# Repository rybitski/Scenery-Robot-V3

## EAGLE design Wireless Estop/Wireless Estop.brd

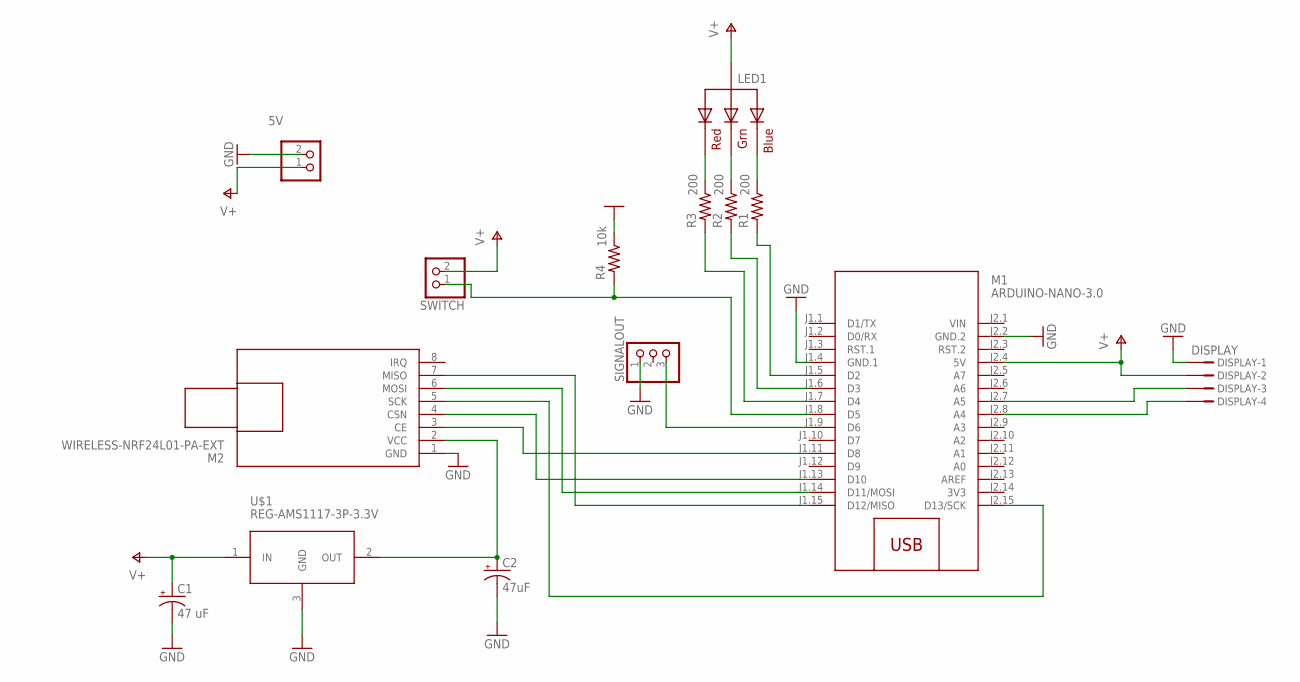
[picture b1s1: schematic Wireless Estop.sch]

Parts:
5V: JST_2PIN-THM; JST-PH-2-THM
C1: 47 uF; E2,5-5
C2: 47uF; E2,5-5
DISPLAY: DISPLAY; B4B-ZR
LED1: RGBLED_CA-5MM; LED5MMRGB
M1: ARDUINO-NANO-3.0
M2: WIRELESS-NRF24L01-PA-EXT
R1, R2, R3: 200; 0805-THM
R4: 10k; 0805-THM
SIGNALOUT: PINHD-1X3; 1X03
SWITCH: PINHD-1X2; 1X02
U$1: REG-AMS1117-3P-3.3V; REG-AMS1117-3P

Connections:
3V3: M1.J2.14 (3V3)
GND: 5V.2 (1), C1.-, C2.-, DISPLAY.1, M1.J1.4 (GND.1), M1.J2.2 (GND.2), M2.1 (GND), R4.1, SIGNALOUT.1, U$1.3 (GND)
unnamed: M1.J1.11 (D8), M2.3 (CE)
unnamed: M1.J1.13 (D10), M2.4 (CSN)
unnamed: M1.J2.15 (D13/SCK), M2.5 (SCK)
unnamed: M1.J1.14 (D11/MOSI), M2.6 (MOSI)
unnamed: M1.J1.15 (D12/MISO), M2.7 (MISO)
unnamed: C2.+, M2.2 (VCC), U$1.2 (OUT)
unnamed: LED1.4 (BLUE), R1.1
unnamed: LED1.3 (GREEN), R2.1
unnamed: LED1.1 (RED), R3.1
unnamed: M1.J1.5 (D2), R1.2
unnamed: M1.J1.6 (D3), R2.2
unnamed: M1.J1.7 (D4), R3.2
unnamed: DISPLAY.4, M1.J2.8 (A4)
unnamed: DISPLAY.3, M1.J2.7 (A5)
unnamed: M1.J1.8 (D5), R4.2, SWITCH.1
unnamed: M1.J1.9 (D6), SIGNALOUT.3
V+: 5V.1 (2), C1.+, DISPLAY.2, LED1.2 (VCC), M1.J2.4 (5V), SWITCH.2, U$1.1 (IN)
VIN: M1.J2.1 (VIN)

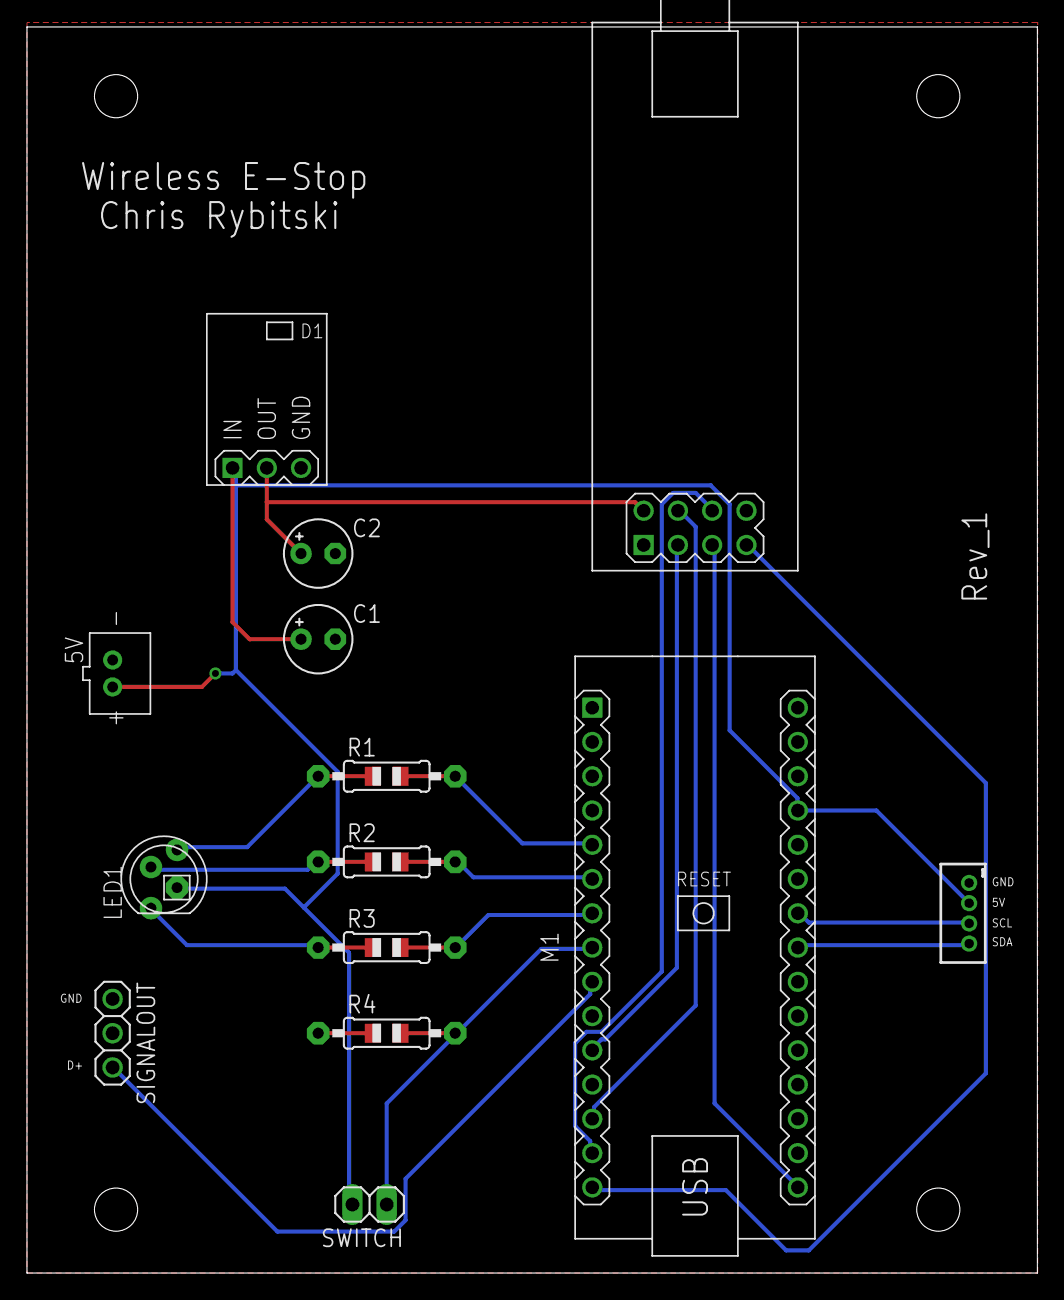
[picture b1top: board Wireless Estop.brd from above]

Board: 2 copper layers, 74.9 x 92.4 mm, 14 parts (0 on the bottom side), 18 nets.

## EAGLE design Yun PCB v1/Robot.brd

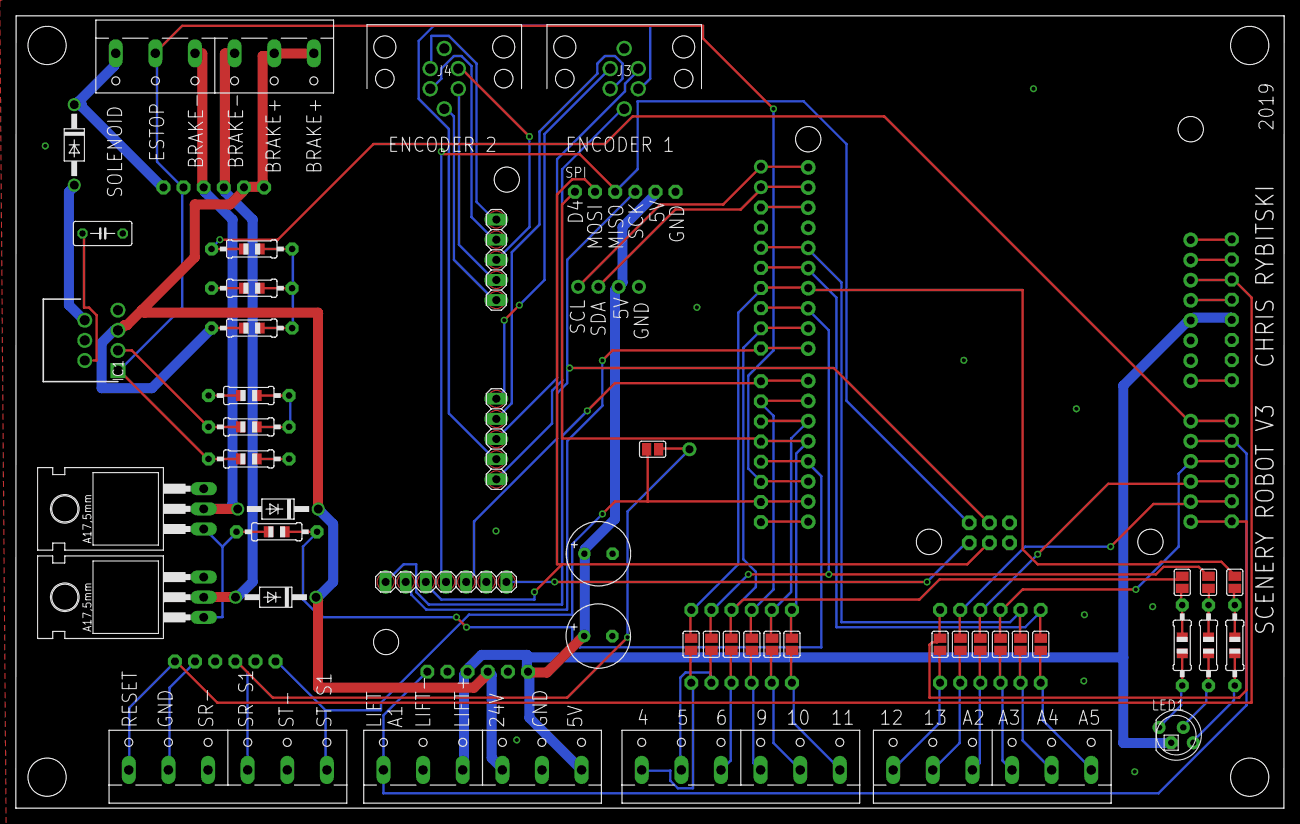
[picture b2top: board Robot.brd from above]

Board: 2 copper layers, 160.0 x 100.0 mm, 66 parts (1 on the bottom side), 73 nets.

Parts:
C5, C7: E3,5-8
C6: 0.1uF; C050-030X075
D1, D2, D3: 1N4004; DO41-10
IC1: DRV102T; TO127P470X1016X2195-7P
J3, J4: 4-2172081-2; 421720812
JP1, JP2: 1X05
JP3: 1X07
JP4, JP7, JP11, JP13, JP14, JP15, JP16, JP17: 1X06-CLEANBIG
JP5, JP6, JP8: 1X08-CLEANBIG
JP9, JP10, JP12, JP18, JP19, JP20, JP21: 1X01-CLEANBIG
LED1: RGBLED_CA-5MM; LED5MMRGB
PCB1: ARDUINO_UNO
Q3, Q4: TIP120; TO220AH
R5, R6, R7: 0805-THM
R9, R10, R14, R15: 10K; 0805-THM
R11: 2.2K; 0805-THM
R12: 20K; 0805-THM
R13: 51K; 0805-THM
SJ1, SJ2, SJ4, SJ5, SJ6, SJ7, SJ8, SJ9, SJ10, SJ11, SJ12, SJ13, SJ14, SJ15, SJ16, SJ17: SJ
SPI: 1X06-CLEANBIG
X1, X2, X3, X4, X5: W237-6

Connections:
3.3V: JP6.5, PCB1.3.3V
+5V: C5.+, C7.+, JP6.4, JP7.1, JP7.4, JP20.1, LED1.2, PCB1.5V, SPI.5, X3.3, X3.6
+24V: D2.C, D3.C, IC1.5, JP4.5, JP4.6, JP7.3, R10.2, X1.1, X1.2, X3.4
A0: JP11.6, PCB1.A0, R9.1, R9.2, R10.1, R11.2
A1: JP7.6, JP11.5, PCB1.A1, X3.1
A2: JP11.4, JP17.4, PCB1.A2, SJ14.1
A3: JP11.3, JP17.3, PCB1.A3, SJ15.1
A4: JP11.2, JP17.2, PCB1.A4, SJ16.1
A5: JP11.1, JP17.1, PCB1.A5, SJ17.1
AREF: JP8.1, PCB1.AREF
ATN: JP6.8, PCB1.N/C
BRAKE1: D3.A, JP4.3, Q3.C, X1.4
BRAKE2: D2.A, JP4.4, Q4.C, X1.3
D0: JP5.8, PCB1.0
D1: JP5.7, JP13.1, PCB1.1, SJ1.1, X2.6
D3: JP5.5, PCB1.3, R15.2
D4: JP5.4, JP16.6, PCB1.4, SJ2.1, SPI.1
D5: JP5.3, JP16.5, PCB1.5, SJ7.1
D6: JP5.2, JP16.4, PCB1.6, SJ8.1
D7: JP3.1, JP5.1, PCB1.7
D8: JP3.2, JP8.8, PCB1.8
D9: JP8.7, JP16.3, PCB1.9, SJ6.1, SJ9.1
D10: JP8.6, JP16.2, PCB1.10, SJ5.1, SJ10.1
D11: JP8.5, JP16.1, PCB1.11, SJ4.1, SJ11.1
D12: JP8.4, JP17.6, PCB1.12, SJ12.1
D13: JP8.3, JP17.5, PCB1.13, SJ13.1
ESTOP-IN: IC1.1, JP4.2, JP5.6, PCB1.2, R14.1, X1.5
GND: C5.-, C6.2, C7.-, IC1.4, JP3.6, JP6.2, JP6.3, JP7.2, JP7.5, JP8.2, JP13.2, JP13.4, JP21.1, PCB1.GND, PCB1.GND., PCB1.GND.., PCB1.GND_, Q3.E, Q4.E, R11.1, R13.2, R14.2, SPI.6, X2.3, X2.5, X3.2, X3.5
I/OREF: JP6.7, PCB1.I/OREF
MISO: JP3.4, PCB1.MISO, SPI.3
MOSI: JP3.3, PCB1.MOSI, SPI.2
unnamed: LED1.1, R7.2
unnamed: LED1.3, R6.2
unnamed: LED1.4, R5.2
unnamed: J3.1, JP1.2
unnamed: J3.2, JP1.3
unnamed: J3.5, JP1.4
unnamed: J3.4, JP1.5
unnamed: J4.1, JP2.2
unnamed: J4.2, JP2.3
unnamed: J4.4, JP2.5
unnamed: J4.5, JP2.4
unnamed: C6.1, IC1.2
unnamed: R12.2, R13.1
unnamed: IC1.3, R12.1
unnamed: D1.A, IC1.6
unnamed: Q3.B, Q4.B, R15.1
unnamed: JP14.1, SJ2.2, X4.6
unnamed: JP14.2, SJ7.2, X4.5
unnamed: JP14.3, SJ8.2, X4.4
unnamed: J3.6, JP1.1
unnamed: JP12.1, JP13.3, SJ1.2, X2.4
unnamed: J4.6, JP2.1
unnamed: JP14.4, SJ9.2, X4.3
unnamed: JP14.5, SJ10.2, X4.2
unnamed: JP14.6, SJ11.2, X4.1
unnamed: JP15.1, SJ12.2, X5.6
unnamed: JP15.2, SJ13.2, X5.5
unnamed: JP15.3, SJ14.2, X5.4
unnamed: JP15.4, SJ15.2, X5.3
unnamed: JP15.5, SJ16.2, X5.2
unnamed: JP15.6, SJ17.2, X5.1
unnamed: JP13.5, X2.2
unnamed: R7.1, SJ6.2
unnamed: R6.1, SJ5.2
unnamed: R5.1, SJ4.2
RESET: JP6.6, JP13.6, PCB1.RESET, X2.1
SCK: JP3.5, PCB1.SCK, SPI.4
SCL: JP10.1, JP18.1, PCB1.SCL
SDA: JP9.1, JP19.1, PCB1.SDA
SOLENOID: D1.C, JP4.1, X1.6
SPIV+: JP3.7, PCB1.+5V
VIN: JP6.1, PCB1.VIN

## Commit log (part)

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2019-03-13 Rename Wireless_Estop_v3_Remote.ino to Wireless Safety Stop/Arduino/Wireless_Estop_v3_Remote.ino
2019-03-13 Rename Wireless_Estop_v3_Robot.ino to Wireless Safety Stop/Arduino/Wireless_Estop_v3_Robot.ino
2019-03-14 Organized Folders
2019-03-15 Added Joes Stuff
    yay
2019-04-26 created wiki.md file (also in the wiki section)
2019-09-19 Merged
    Merging from joes repo
2019-09-19 Newer Update
2019-09-20 9/20 update
2019-09-20 Initial Commit
    Added firmware and middleware
2019-09-20 Adding firmware and middleware
    These files were previously missing and are required for operation.
2019-09-20 Friday meeting update
    Fixed drive code over specified distance
2019-09-25 Adding missing flash and pip
    Images required to complete YUN Guide and the pip tar file
2019-10-11 Created a method to parseJson and a test file
2019-10-11 safety stop code
2019-10-17 MiniBot
    Code for MiniBot subproject
2019-10-18 Kang speculative code
2019-10-30 Update accel/decel
    WIP
2019-11-01 Fixed drifting issue
    Dec still broken
2019-11-01 meeting
2019-11-06 MiniBot V1 Completion
2019-11-06 Rewrite for V2
2019-11-07 Stack Exchange implemented
2019-11-07 Changed from "and' to &&
2019-11-20 Added cue data to V3
2019-11-20 fixed bugs in last commit
2019-12-10 V3 folder
2019-12-28 Bump handlebars from 4.1.0 to 4.5.3 in /client-master
    Bumps [handlebars](https://github.com/wycats/handlebars.js) from 4.1.0 to 4.5.3.
    - [Release notes](https://github.com/wycats/handlebars.js/releases)
    - [Changelog](https://github.com/wycats/handlebars.js/blob/master/release-notes.md)
    - [Commits](https://github.com/wycats/handlebars.js/compare/v4.1.0...v4.5.3)
2020-03-14 Bump acorn from 5.7.3 to 5.7.4 in /client-master
    Bumps [acorn](https://github.com/acornjs/acorn) from 5.7.3 to 5.7.4.
    - [Release notes](https://github.com/acornjs/acorn/releases)
    - [Commits](https://github.com/acornjs/acorn/compare/5.7.3...5.7.4)
2020-06-06 Bump websocket-extensions from 0.1.3 to 0.1.4 in /client-master
    Bumps [websocket-extensions](https://github.com/faye/websocket-extensions-node) from 0.1.3 to 0.1.4.
    - [Release notes](https://github.com/faye/websocket-extensions-node/releases)
    - [Changelog](https://github.com/faye/websocket-extensions-node/blob/master/CHANGELOG.md)
    - [Commits](https://github.com/faye/websocket-extensions-node/compare/0.1.3...0.1.4)
2020-07-30 Bump elliptic from 6.4.1 to 6.5.3 in /client-master
    Bumps [elliptic](https://github.com/indutny/elliptic) from 6.4.1 to 6.5.3.
    - [Release notes](https://github.com/indutny/elliptic/releases)
    - [Commits](https://github.com/indutny/elliptic/compare/v6.4.1...v6.5.3)
2020-09-04 Bump handlebars from 4.1.0 to 4.7.6 in /client-master
    Bumps [handlebars](https://github.com/wycats/handlebars.js) from 4.1.0 to 4.7.6.
    - [Release notes](https://github.com/wycats/handlebars.js/releases)
    - [Changelog](https://github.com/handlebars-lang/handlebars.js/blob/master/release-notes.md)
    - [Commits](https://github.com/wycats/handlebars.js/compare/v4.1.0...v4.7.6)
2020-09-07 Bump http-proxy from 1.17.0 to 1.18.1 in /client-master
    Bumps [http-proxy](https://github.com/http-party/node-http-proxy) from 1.17.0 to 1.18.1.
    - [Release notes](https://github.com/http-party/node-http-proxy/releases)
    - [Changelog](https://github.com/http-party/node-http-proxy/blob/master/CHANGELOG.md)
    - [Commits](https://github.com/http-party/node-http-proxy/compare/1.17.0...1.18.1)
2021-03-09 Bump elliptic from 6.4.1 to 6.5.4 in /client-master
    Bumps [elliptic](https://github.com/indutny/elliptic) from 6.4.1 to 6.5.4.
    - [Release notes](https://github.com/indutny/elliptic/releases)
    - [Commits](https://github.com/indutny/elliptic/compare/v6.4.1...v6.5.4)
2021-03-30 Bump y18n from 3.2.1 to 3.2.2 in /client-master
    Bumps [y18n](https://github.com/yargs/y18n) from 3.2.1 to 3.2.2.
    - [Release notes](https://github.com/yargs/y18n/releases)
    - [Changelog](https://github.com/yargs/y18n/blob/master/CHANGELOG.md)
    - [Commits](https://github.com/yargs/y18n/commits)
2021-04-19 Bump ssri from 6.0.1 to 6.0.2 in /client-master
    Bumps [ssri](https://github.com/npm/ssri) from 6.0.1 to 6.0.2.
    - [Release notes](https://github.com/npm/ssri/releases)
    - [Changelog](https://github.com/npm/ssri/blob/v6.0.2/CHANGELOG.md)
    - [Commits](https://github.com/npm/ssri/compare/v6.0.1...v6.0.2)
2021-05-07 Bump url-parse from 1.4.4 to 1.5.1 in /client-master
    Bumps [url-parse](https://github.com/unshiftio/url-parse) from 1.4.4 to 1.5.1.
    - [Release notes](https://github.com/unshiftio/url-parse/releases)
    - [Commits](https://github.com/unshiftio/url-parse/compare/1.4.4...1.5.1)
2021-05-10 Bump hosted-git-info from 2.7.1 to 2.8.9 in /client-master
    Bumps [hosted-git-info](https://github.com/npm/hosted-git-info) from 2.7.1 to 2.8.9.
    - [Release notes](https://github.com/npm/hosted-git-info/releases)
    - [Changelog](https://github.com/npm/hosted-git-info/blob/v2.8.9/CHANGELOG.md)
    - [Commits](https://github.com/npm/hosted-git-info/compare/v2.7.1...v2.8.9)
2021-05-27 Bump dns-packet from 1.3.1 to 1.3.4 in /client-master
    Bumps [dns-packet](https://github.com/mafintosh/dns-packet) from 1.3.1 to 1.3.4.
    - [Release notes](https://github.com/mafintosh/dns-packet/releases)
    - [Changelog](https://github.com/mafintosh/dns-packet/blob/master/CHANGELOG.md)
    - [Commits](https://github.com/mafintosh/dns-packet/compare/v1.3.1...v1.3.4)
2021-06-07 Bump merge-deep from 3.0.2 to 3.0.3 in /client-master
    Bumps [merge-deep](https://github.com/jonschlinkert/merge-deep) from 3.0.2 to 3.0.3.
    - [Release notes](https://github.com/jonschlinkert/merge-deep/releases)
    - [Commits](https://github.com/jonschlinkert/merge-deep/compare/3.0.2...3.0.3)
    ---
    updated-dependencies:
    - dependency-name: merge-deep
2021-08-10 Bump path-parse from 1.0.6 to 1.0.7 in /client-master
    Bumps [path-parse](https://github.com/jbgutierrez/path-parse) from 1.0.6 to 1.0.7.
    - [Release notes](https://github.com/jbgutierrez/path-parse/releases)
    - [Commits](https://github.com/jbgutierrez/path-parse/commits/v1.0.7)
    ---
    updated-dependencies:
    - dependency-name: path-parse
2021-09-21 Bump tmpl from 1.0.4 to 1.0.5 in /client-master
    Bumps [tmpl](https://github.com/daaku/nodejs-tmpl) from 1.0.4 to 1.0.5.
    - [Release notes](https://github.com/daaku/nodejs-tmpl/releases)
    - [Commits](https://github.com/daaku/nodejs-tmpl/commits/v1.0.5)
    ---
    updated-dependencies:
    - dependency-name: tmpl
2021-10-05 Bump url-parse from 1.4.4 to 1.5.3 in /client-master
    Bumps [url-parse](https://github.com/unshiftio/url-parse) from 1.4.4 to 1.5.3.
    - [Release notes](https://github.com/unshiftio/url-parse/releases)
    - [Commits](https://github.com/unshiftio/url-parse/compare/1.4.4...1.5.3)
    ---
    updated-dependencies:
    - dependency-name: url-parse
2022-01-13 Bump follow-redirects from 1.6.1 to 1.14.7 in /client-master
    Bumps [follow-redirects](https://github.com/follow-redirects/follow-redirects) from 1.6.1 to 1.14.7.
    - [Release notes](https://github.com/follow-redirects/follow-redirects/releases)
    - [Commits](https://github.com/follow-redirects/follow-redirects/compare/v1.6.1...v1.14.7)
    ---
    updated-dependencies:
    - dependency-name: follow-redirects
2022-02-11 Bump ajv from 6.9.1 to 6.12.6 in /client-master
    Bumps [ajv](https://github.com/ajv-validator/ajv) from 6.9.1 to 6.12.6.
    - [Release notes](https://github.com/ajv-validator/ajv/releases)
    - [Commits](https://github.com/ajv-validator/ajv/compare/v6.9.1...v6.12.6)
    ---
    updated-dependencies:
    - dependency-name: ajv
2022-02-12 Bump follow-redirects from 1.6.1 to 1.14.8 in /client-master
    Bumps [follow-redirects](https://github.com/follow-redirects/follow-redirects) from 1.6.1 to 1.14.8.
    - [Release notes](https://github.com/follow-redirects/follow-redirects/releases)
    - [Commits](https://github.com/follow-redirects/follow-redirects/compare/v1.6.1...v1.14.8)
    ---
    updated-dependencies:
    - dependency-name: follow-redirects
2022-02-17 Bump url-parse from 1.4.4 to 1.5.7 in /client-master
    Bumps [url-parse](https://github.com/unshiftio/url-parse) from 1.4.4 to 1.5.7.
    - [Release notes](https://github.com/unshiftio/url-parse/releases)
    - [Commits](https://github.com/unshiftio/url-parse/compare/1.4.4...1.5.7)
    ---
    updated-dependencies:
    - dependency-name: url-parse
2022-06-01 Bump eventsource from 1.0.7 to 1.1.1 in /client-master
    Bumps [eventsource](https://github.com/EventSource/eventsource) from 1.0.7 to 1.1.1.
    - [Release notes](https://github.com/EventSource/eventsource/releases)
    - [Changelog](https://github.com/EventSource/eventsource/blob/master/HISTORY.md)
    - [Commits](https://github.com/EventSource/eventsource/compare/v1.0.7...v1.1.1)
    ---
    updated-dependencies:
2022-10-05 Bump css-what from 2.1.2 to 2.1.3 in /client-master
    Bumps [css-what](https://github.com/fb55/css-what) from 2.1.2 to 2.1.3.
    - [Release notes](https://github.com/fb55/css-what/releases)
    - [Commits](https://github.com/fb55/css-what/compare/v2.1.2...v2.1.3)
    ---
    updated-dependencies:
    - dependency-name: css-what
2022-11-18 Bump loader-utils and react-scripts in /client-master
    Bumps [loader-utils](https://github.com/webpack/loader-utils) to 2.0.4 and updates ancestor dependency [react-scripts](https://github.com/facebook/create-react-app/tree/HEAD/packages/react-scripts). 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
    Updates `loader-utils` from 1.2.3 to 2.0.4
    - [Release notes](https://github.com/webpack/loader-utils/releases)
    - [Changelog](https://github.com/webpack/loader-utils/blob/v2.0.4/CHANGELOG.md)
    - [Commits](https://github.com/webpack/loader-utils/compare/v1.2.3...v2.0.4)
    Updates `react-scripts` from 2.1.5 to 5.0.1
2022-12-03 Bump decode-uri-component from 0.2.0 to 0.2.2 in /client-master
    Bumps [decode-uri-component](https://github.com/SamVerschueren/decode-uri-component) from 0.2.0 to 0.2.2.
    - [Release notes](https://github.com/SamVerschueren/decode-uri-component/releases)
    - [Commits](https://github.com/SamVerschueren/decode-uri-component/compare/v0.2.0...v0.2.2)
    ---
    updated-dependencies:
    - dependency-name: decode-uri-component
2022-12-08 Bump qs from 6.5.2 to 6.11.0 in /middleman-master
    Bumps [qs](https://github.com/ljharb/qs) from 6.5.2 to 6.11.0.
    - [Release notes](https://github.com/ljharb/qs/releases)
    - [Changelog](https://github.com/ljharb/qs/blob/main/CHANGELOG.md)
    - [Commits](https://github.com/ljharb/qs/compare/v6.5.2...v6.11.0)
    ---
    updated-dependencies:
2022-12-09 Bump express from 4.16.4 to 4.17.3 in /middleman-master
    Bumps [express](https://github.com/expressjs/express) from 4.16.4 to 4.17.3.
    - [Release notes](https://github.com/expressjs/express/releases)
    - [Changelog](https://github.com/expressjs/express/blob/master/History.md)
    - [Commits](https://github.com/expressjs/express/compare/4.16.4...4.17.3)
    ---
    updated-dependencies:
2022-12-09 Bump express from 4.16.4 to 4.18.2 in /client-master
    Bumps [express](https://github.com/expressjs/express) from 4.16.4 to 4.18.2.
    - [Release notes](https://github.com/expressjs/express/releases)
    - [Changelog](https://github.com/expressjs/express/blob/master/History.md)
    - [Commits](https://github.com/expressjs/express/compare/4.16.4...4.18.2)
    ---
    updated-dependencies:

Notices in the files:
parts and their libraries:
diy-modules: Released under the Creative Commons Attribution 4.0 International License: http://creativecommons.org/licenses/by/4.0
